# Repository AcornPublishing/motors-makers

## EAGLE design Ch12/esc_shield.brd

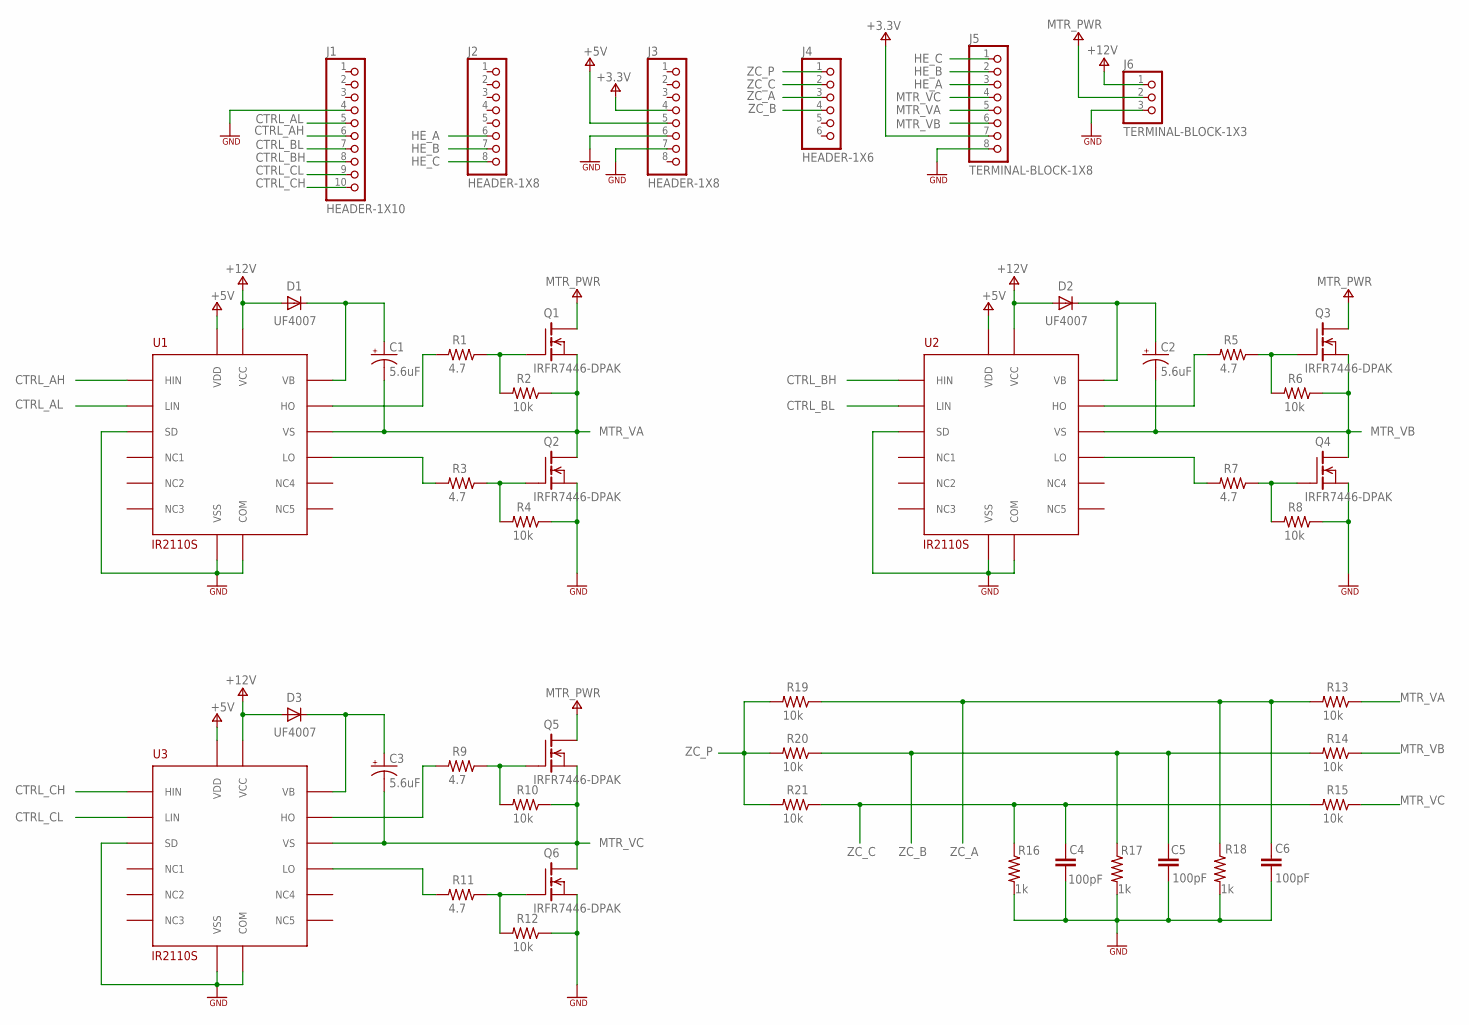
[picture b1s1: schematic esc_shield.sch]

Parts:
C1, C2, C3: 5.6uF; EIA7343-31
C4, C5, C6: 100pF; SMD0603
D1, D2, D3: UF4007; DO41-10
J1: HEADER-1X10; 1X10
J2, J3: HEADER-1X8; 1X08
J4: HEADER-1X6; 1X06
J5: TERMINAL-BLOCK-1X8; 1X08
J6: TERMINAL-BLOCK-1X3; 1X03
Q1, Q2, Q3, Q4, Q5, Q6: IRFR7446-DPAK; TO252AA
R1, R3, R5, R7, R9, R11: 4.7; SMD0603
R2, R4, R6, R8, R10, R12, R13, R14, R15, R19, R20, R21: 10k; SMD0603
R16, R17, R18: 1k; SMD0603
U1, U2, U3: IR2110S; SO16L

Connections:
3.3V: J3.4, J5.7
5V: J3.5, U1.11 (VDD), U2.11 (VDD), U3.11 (VDD)
12V: D1.A, D2.A, D3.A, J6.1, U1.3 (VCC), U2.3 (VCC), U3.3 (VCC)
BETWEEN_CAP_AND_DIODE: C1.+, D1.C, U1.7 (VB)
BETWEEN_CAP_AND_DIODE_2: C2.+, D2.C, U2.7 (VB)
CTRL_AH: J1.6, U1.12 (HIN)
CTRL_AL: J1.5, U1.14 (LIN)
CTRL_BH: J1.8, U2.12 (HIN)
CTRL_BL: J1.7, U2.14 (LIN)
CTRL_CH: J1.10, U3.12 (HIN)
CTRL_CL: J1.9, U3.14 (LIN)
GND: C4.2, C5.2, C6.2, J1.4, J3.6, J3.7, J5.8, J6.3, Q2.3 (S), Q4.3 (S), Q6.3 (S), R4.1, R8.1, R12.1, R16.2, R17.2, R18.2, U1.2 (COM), U1.13 (SD), U1.15 (VSS), U2.2 (COM), U2.13 (SD), U2.15 (VSS), U3.2 (COM), U3.13 (SD), U3.15 (VSS)
HE_A: J2.6, J5.3
HE_B: J2.7, J5.2
HE_C: J2.8, J5.1
MTR_PWR: J6.2, Q1.4 (D), Q3.4 (D), Q5.4 (D)
MTR_VA: C1.-, J5.5, Q1.3 (S), Q2.4 (D), R2.1, R13.1, U1.6 (VS)
MTR_VB: C2.-, J5.6, Q3.3 (S), Q4.4 (D), R6.1, R14.1, U2.6 (VS)
MTR_VC: C3.-, J5.4, Q5.3 (S), Q6.4 (D), R10.1, R15.1, U3.6 (VS)
unnamed: Q6.1 (G), R11.1, R12.2
unnamed: Q1.1 (G), R1.1, R2.2
unnamed: Q4.1 (G), R7.1, R8.2
unnamed: Q3.1 (G), R5.1, R6.2
unnamed: R11.2, U3.1 (LO)
unnamed: Q2.1 (G), R3.1, R4.2
unnamed: C3.+, D3.C, U3.7 (VB)
unnamed: R9.2, U3.8 (HO)
unnamed: Q5.1 (G), R9.1, R10.2
TO_Q1_GATE: R1.2, U1.8 (HO)
TO_Q2_GATE: R3.2, U1.1 (LO)
TO_Q3_GATE: R5.2, U2.8 (HO)
TO_Q4_GATE: R7.2, U2.1 (LO)
ZC_A: C6.1, J4.3, R13.2, R18.1, R19.1
ZC_B: C5.1, J4.4, R14.2, R17.1, R20.1
ZC_C: C4.1, J4.2, R15.2, R16.1, R21.1
ZC_P: J4.1, R19.2, R20.2, R21.2

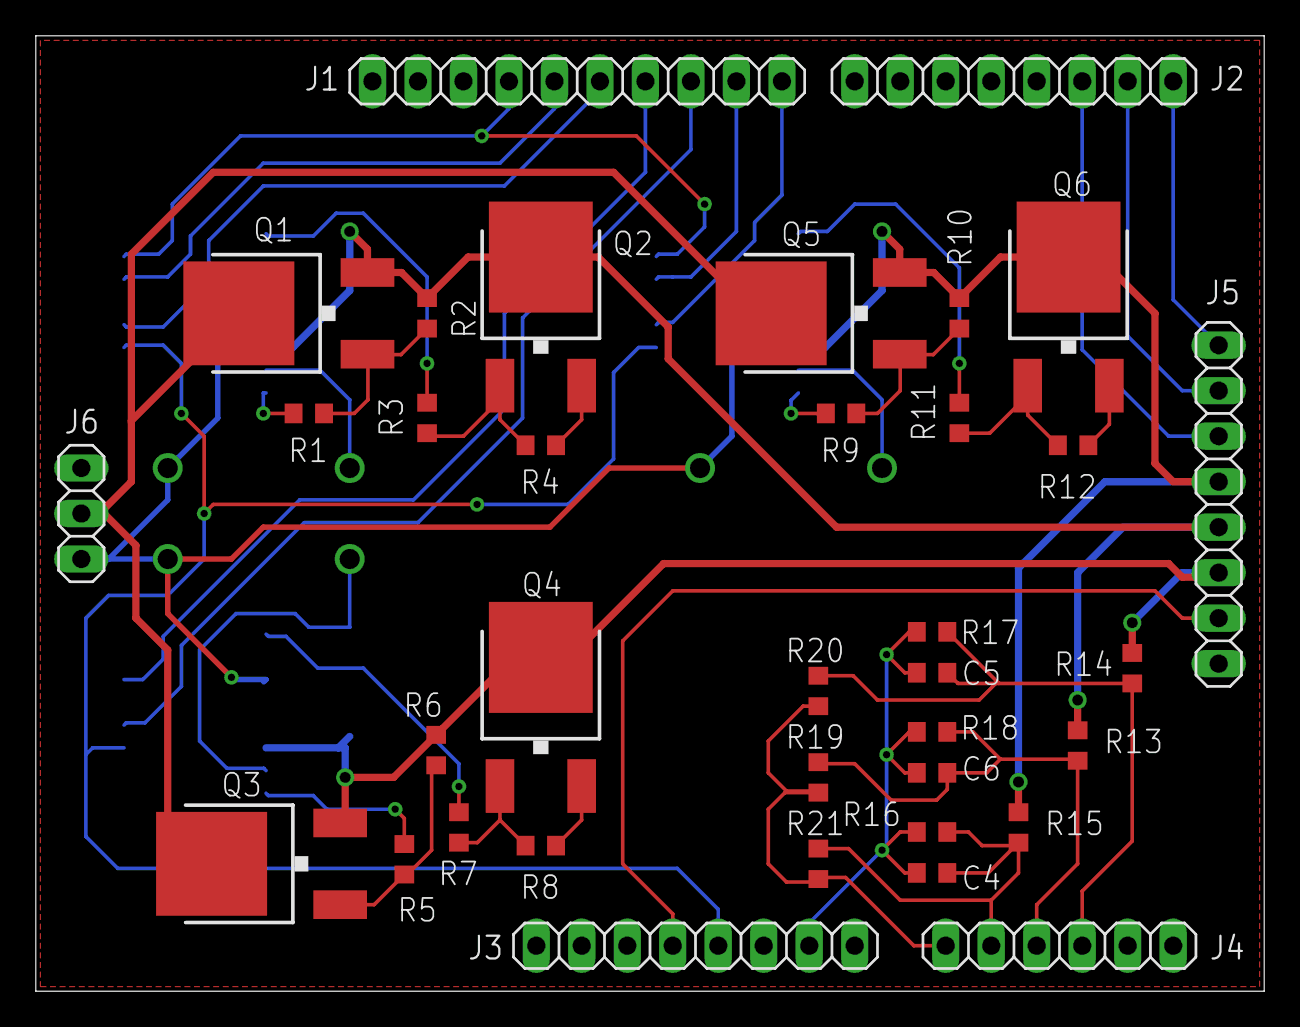
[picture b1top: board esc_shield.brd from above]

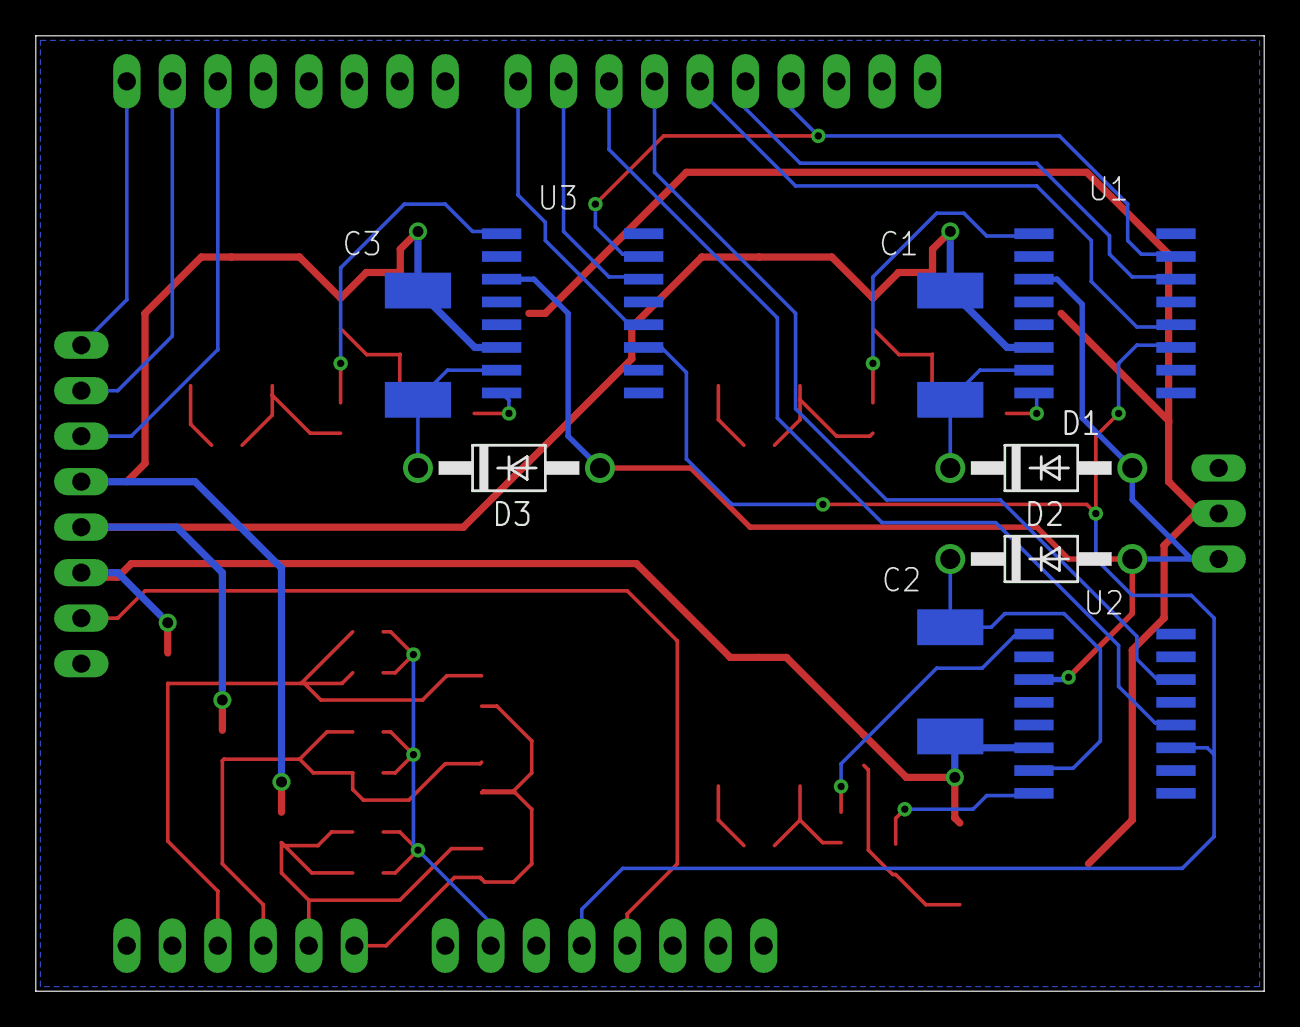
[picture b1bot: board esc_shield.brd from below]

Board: 2 copper layers, 68.6 x 53.3 mm, 45 parts (9 on the bottom side), 36 nets.

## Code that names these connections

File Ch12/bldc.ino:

/* This sketch controls a BLDC by applying voltage to the
   six switches on the ESC Shield discussed in Chapter 12 */

// Assign names to the pins
int i, t, va, vp;
int old_time, zc_interval;
int ctrl_ah = 13;
int ctrl_al = 12;
int ctrl_bh = 11;
int ctrl_bl = 10;
int ctrl_ch = 9;
int ctrl_cl = 8;
int zc_a = 0;
int zc_b = 1;
int zc_c = 2;
int zc_p = 3;

int time_goal = 50;

void setup() {
  
  // Bring rotor to a known initial position
  for (i=0; i<255; i+=5){
    analogWrite(ctrl_ah, i);
    analogWrite(ctrl_bl, i);
    analogWrite(ctrl_cl, i);    
    delay(60);                  
  }
  
  // Set initial timing value
  old_time = millis();
  
  // Start turning the rotor slowly
  for (t=500; t>200; t-=50) {
    rotate(t);
  }
  t = 200;
}

void loop() { 
  
  // Check for zero-crossing
  vp = analogRead(zc_p);
  va = analogRead(zc_a);
  if((vp - va < 10) || (va - vp < 10)) {
    zc_interval = millis() - old_time;
    old_time = millis();
    if(zc_interval - time_goal > 50) {
      t -= 25;
    }
    else if(time_goal - zc_interval > 50) {
      t += 25;
    }
  }
  
  // Rotate the BLDC
  rotate(t);
}

// Rotate the motor at the given value of t
void rotate(int t) {
  digitalWrite(ctrl_ah, HIGH);
  digitalWrite(ctrl_al, LOW);  
  digitalWrite(ctrl_bh, LOW);    
  digitalWrite(ctrl_bl, HIGH);
  digitalWrite(ctrl_ch, LOW);    
  digitalWrite(ctrl_cl, LOW);
  delay(t);
  
  digitalWrite(ctrl_ah, HIGH);
  digitalWrite(ctrl_al, LOW);  
  digitalWrite(ctrl_bh, LOW);    
  digitalWrite(ctrl_bl, LOW);
  digitalWrite(ctrl_ch, LOW);    
  digitalWrite(ctrl_cl, HIGH);
  delay(t); 
  
  digitalWrite(ctrl_ah, LOW);
  digitalWrite(ctrl_al, LOW);  
  digitalWrite(ctrl_bh, HIGH);    
  digitalWrite(ctrl_bl, LOW);
  digitalWrite(ctrl_ch, LOW);    
  digitalWrite(ctrl_cl, HIGH);
  delay(t);   
  
  digitalWrite(ctrl_ah, LOW);
  digitalWrite(ctrl_al, HIGH);  
  digitalWrite(ctrl_bh, HIGH);    
  digitalWrite(ctrl_bl, LOW);
  digitalWrite(ctrl_ch, LOW);    
  digitalWrite(ctrl_cl, LOW);
  delay(t);
  
  digitalWrite(ctrl_ah, LOW);
  digitalWrite(ctrl_al, HIGH);  
  digitalWrite(ctrl_bh, LOW);    
  digitalWrite(ctrl_bl, LOW);
  digitalWrite(ctrl_ch, HIGH);    
  digitalWrite(ctrl_cl, LOW);
  delay(t); 
  
  digitalWrite(ctrl_ah, LOW);
  digitalWrite(ctrl_al, LOW);  
  digitalWrite(ctrl_bh, LOW);    
  digitalWrite(ctrl_bl, HIGH);
  digitalWrite(ctrl_ch, HIGH);    
  digitalWrite(ctrl_cl, LOW);
  delay(t);   
}

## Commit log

2022-02-28 motors-makers
    메이커를 위한 실전 모터 가이드 [다양한 모터 개념과 설정 방법]
